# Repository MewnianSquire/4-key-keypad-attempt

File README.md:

# 4-key-tutorial-keypad
 An Attempt At Making a Custom 4 Key Keypad

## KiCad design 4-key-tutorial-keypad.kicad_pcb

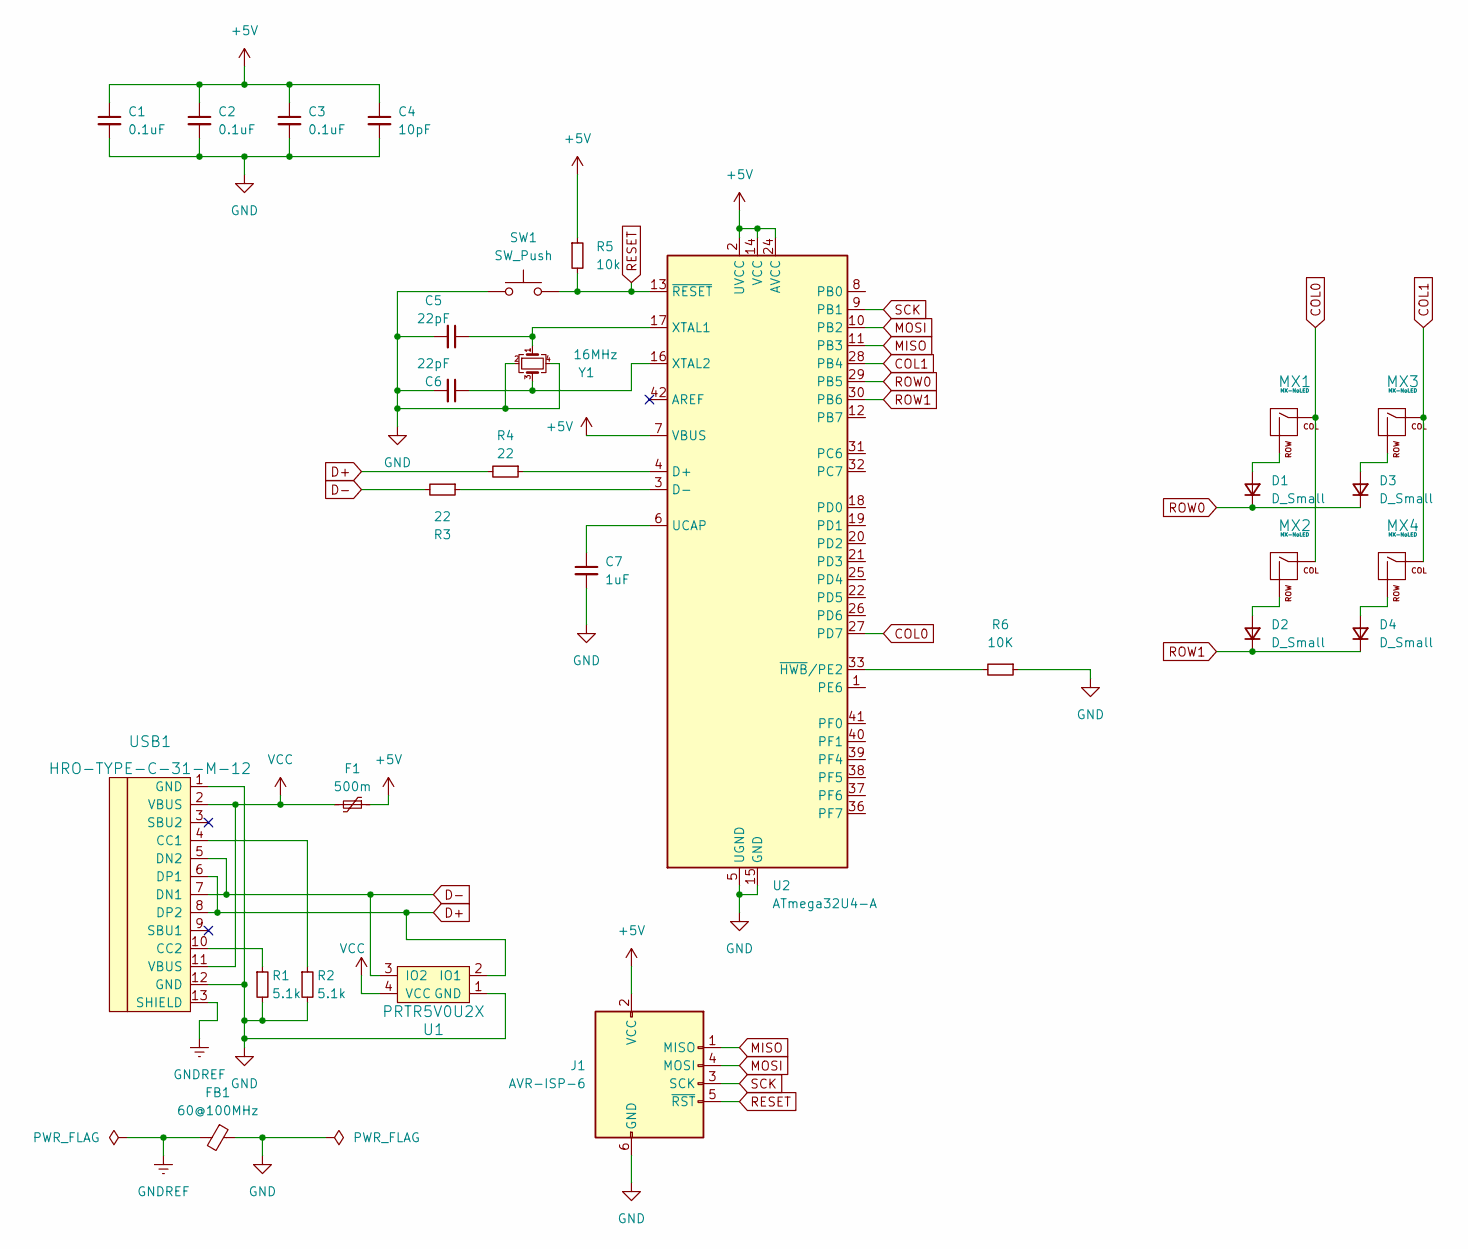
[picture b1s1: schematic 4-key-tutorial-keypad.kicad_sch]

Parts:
C1, C2, C3: 0.1uF; C_0805_2012Metric_Pad1.18x1.45mm_HandSolder
C4: 10pF; C_0805_2012Metric_Pad1.18x1.45mm_HandSolder
C5, C6: 22pF; C_0805_2012Metric_Pad1.18x1.45mm_HandSolder
C7: 1uF; C_0805_2012Metric_Pad1.18x1.45mm_HandSolder
D1, D2, D3, D4: D_Small; D_SOD-123
F1: 500m; D_1206_3216Metric_Pad1.42x1.75mm_HandSolder
FB1: 60@100MHz; L_0805_2012Metric_Pad1.15x1.40mm_HandSolder
J1: AVR-ISP-6; Reset_Pretty-Mask
MX1, MX2, MX3, MX4: MX-NoLED; MX-1U-NoLED
R1, R2: 5.1k; R_0805_2012Metric_Pad1.20x1.40mm_HandSolder
R3, R4: 22; R_0805_2012Metric_Pad1.20x1.40mm_HandSolder
R5: 10k; R_0805_2012Metric_Pad1.20x1.40mm_HandSolder
R6: 10K; R_0805_2012Metric_Pad1.20x1.40mm_HandSolder
SW1: SW_Push; SKQG-1155865
U1: PRTR5V0U2X; SOT143B
U2: ATmega32U4-A; TQFP-44_10x10mm_P0.8mm
USB1: HRO-TYPE-C-31-M-12; HRO-TYPE-C-31-M-12-HandSoldering
Y1: 16MHz; Crystal_SMD_3225-4Pin_3.2x2.5mm_HandSoldering

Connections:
+5V: C1.1, C2.1, C3.1, C4.1, F1.1, J1.2 (VCC), R5.1, U2.2 (UVCC), U2.7 (VBUS), U2.14 (VCC), U2.24 (AVCC), U2.34 (VCC), U2.44 (AVCC)
COL0: MX1.1 (COL), MX2.1 (COL), U2.27 (PD7)
COL1: MX3.1 (COL), MX4.1 (COL), U2.28 (PB4)
D+: R4.2, U1.2 (IO1), USB1.6 (DP1), USB1.8 (DP2)
D-: R3.2, U1.3 (IO2), USB1.5 (DN2), USB1.7 (DN1)
GND: C1.2, C2.2, C3.2, C4.2, C5.2, C6.2, C7.2, FB1.1, J1.6 (GND), R1.2, R2.2, R6.1, SW1.1, U1.1 (GND), U2.5 (UGND), U2.15 (GND), U2.23 (GND), U2.35 (GND), U2.43 (GND), USB1.1 (GND), USB1.12 (GND), Y1.2, Y1.4
GNDREF: FB1.2, USB1.13 (SHIELD)
MISO: J1.1 (MISO), U2.11 (PB3)
MOSI: J1.4 (MOSI), U2.10 (PB2)
unnamed: C5.1, U2.17 (XTAL1), Y1.1
unnamed: C6.1, U2.16 (XTAL2), Y1.3
unnamed: C7.1, U2.6 (UCAP)
unnamed: D1.2 (A), MX1.2 (ROW)
unnamed: D2.2 (A), MX2.2 (ROW)
unnamed: D3.2 (A), MX3.2 (ROW)
unnamed: D4.2 (A), MX4.2 (ROW)
unnamed: R1.1, USB1.10 (CC2)
unnamed: R2.1, USB1.4 (CC1)
unnamed: R3.1, U2.3 (D-)
unnamed: R4.1, U2.4 (D+)
unnamed: R6.2, U2.33 (~HWB/PE2)
RESET: J1.5 (~RST), R5.2, SW1.2, U2.13 (~RESET)
ROW0: D1.1 (K), D3.1 (K), U2.29 (PB5)
ROW1: D2.1 (K), D4.1 (K), U2.30 (PB6)
SCK: J1.3 (SCK), U2.9 (PB1)
VCC: F1.2, U1.4 (VCC), USB1.2 (VBUS), USB1.11 (VBUS)

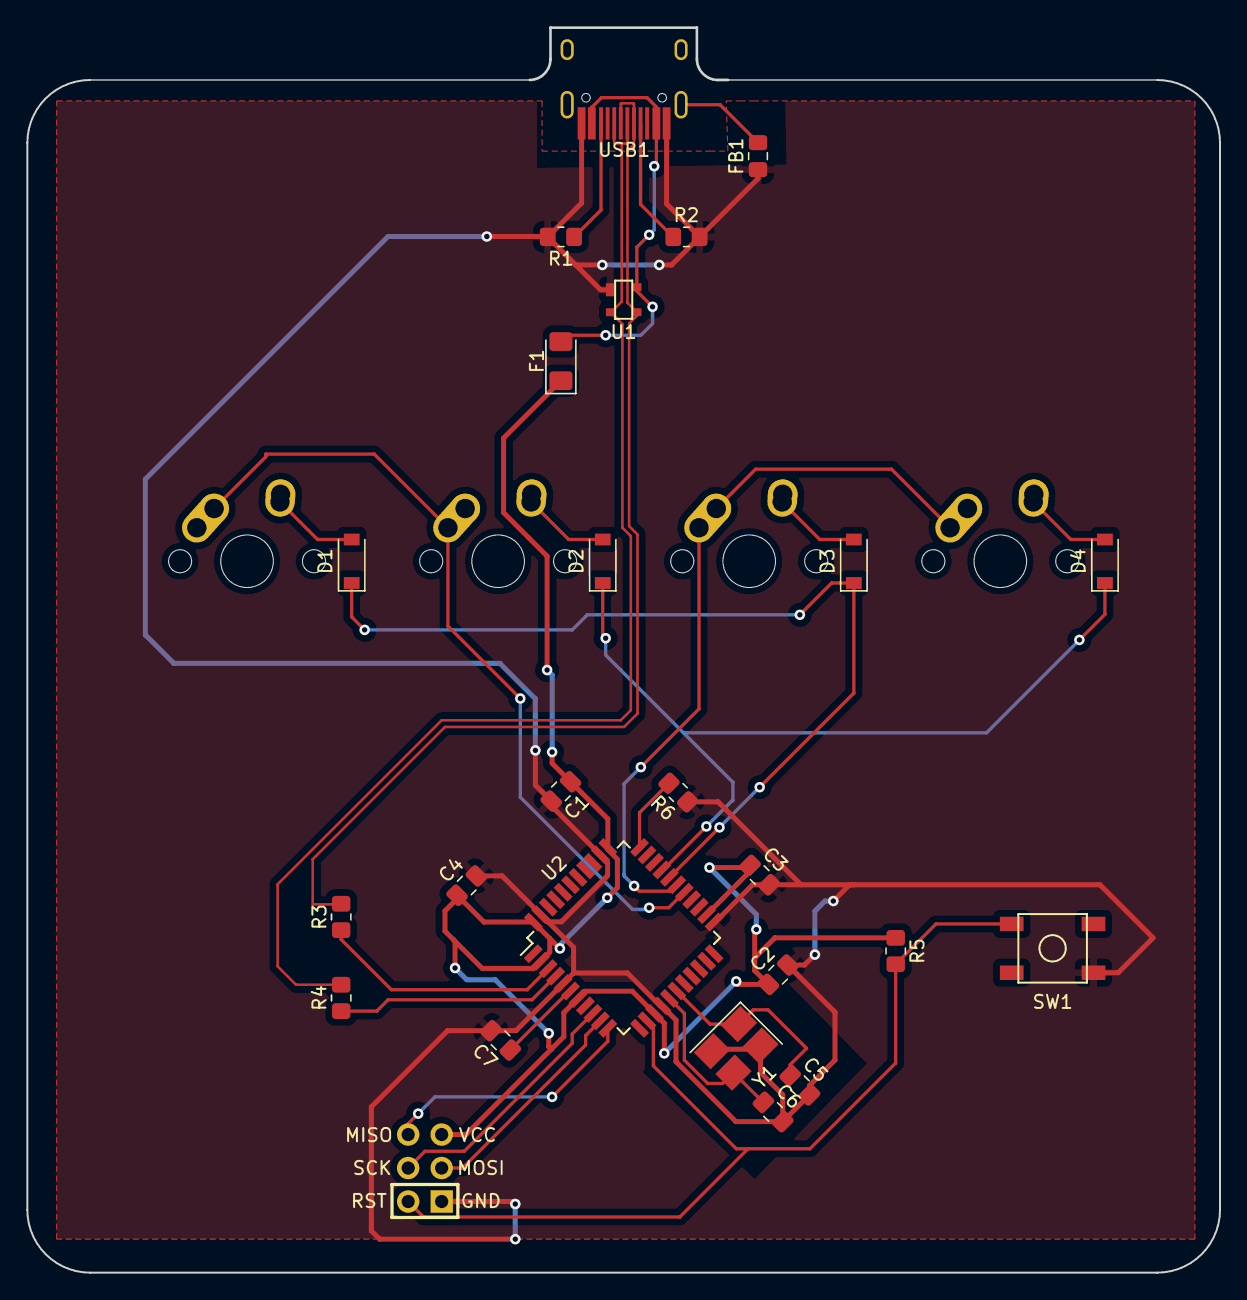
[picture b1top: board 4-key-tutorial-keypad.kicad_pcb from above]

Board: 2 copper layers, 90.4 x 94.4 mm, 29 parts (0 on the bottom side), 26 nets.

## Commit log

2022-06-30 Files on KiCad
    Created the save files on KiCad 6.0.6
2022-06-30 Added Libraries
    3 libs for switch footprint and keyboard components
2022-06-30 Extra lib
    Extra lib for random keyboard components
2022-06-30 KiCad Configuration
    Added the libs into KiCad
